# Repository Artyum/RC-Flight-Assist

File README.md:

# RC Flight Assist (RCFA) Telemetry System

RCFA is a telemetry system for RC pilots, designed specifically for outdoor pattern flying, such as F3A or F3M classes. The system provides better control over the airplane during acrobatics by implementing a radio telemetry mechanism that accurately indicates the position within the flight area. With RCFA, pilots can maintain the proper position in the sky, resulting in better handling and improved skills. The system was tested in collaboration with the top Polish F3A pilot of 2015.

#### How Does It Work?

The RCFA system comprises two separate electronic devices: the Transmitter and the Receiver. The primary role of the Transmitter is to get the 3D or 2D position from GPS and altimeter sensors and send the data to the pilot’s Receiver. The Receiver converts the signal into sound patterns, which the pilot can hear through the built-in speaker or headphones to receive telemetry information.

The basic usage of the RCFA involves defining two points on the ground to determine the flight area. The first point (P1) is the pilot’s position, where the airplane will be controlled from. The second point (P2) is the direction to the flight line where the airplane shall be controlled. These points can be set by walking with the RCFA to the desired positions on the airfield or by writing the coordinates in the configuration file (rcfa.ini). The optimal distance between P1 and P2 depends on GPS signal strength and usually does not need to be more than 20m.

#### Setting Up the Flight Area

Once points P1 and P2 are set within the Transmitter, the RCFA system automatically calculates the remaining flight area coordinates based on preset options: the ideal Flight Line (marked with points A, B, and C), the Green Zone (green color), and the Flight Area (blue color). The pilot’s job is to keep the airplane between the green rectangles.

During a flight, the RCFA Receiver generates tones that change according to the airplane’s distance from the Green Zone. This allows the pilot to react quickly and steer the airplane to the desired position in the sky. The pilot will know exactly how far the airplane is from the flight line, and whether it is ahead or behind the Green Zone, too high, or too far to the left or right side of the Flight Area.

#### Post-Flight Scoring

When the flight is over, the system calculates a score based on the time spent in the zone and overall flight time. This score is automatically stored in a KML file. The logger file can be opened instantly in Google Earth (Windows or Linux) to examine the flight and check the scoring.

#### Additional Features of the RCFA

**GPS Logger**: The system is highly customizable. Users can change various parameters such as the distance from the pilot to the flight line, area angle, flight plane width, and more (nearly 30 options). It has an integrated MicroSD slot for a memory card, which is used to store and read area parameters and to write position data as a high-accuracy GPS Logger. The system implements unique filter algorithms, ensuring high accuracy in the GPS data stream and altitude measurements. The RCFA also allows the use of a barometer for even more accurate altitude measurement. The Logger writes data directly in KML format, which can be instantly opened in Google Earth.

**Real-Time Tracking**: The RCFA can stream data to the Receiver about current 3D coordinates through the RX/TX interface (USB2TTL). The data stream (longitude, latitude, and altitude) can be read and visualized on a PC in real-time. Depending on barometer availability, the altitude data can be taken from GPS or barometer. Users can choose either absolute (mean sea level) or relative (to the pilot’s position) altitude readings.

**Variometer**: The RCFA includes a variometer feature, which can be used in gliders and other types of RC airplanes. The variometer can use GPS data or a barometer to indicate altitude changes. The data is sent to the Receiver, allowing the pilot to control descending or ascending in real-time.

# Overview
https://www.youtube.com/watch?v=m0nCrscLPIs

#### RC Flight Assist - Real-time tracking demo
https://www.youtube.com/watch?v=_wvuzFEu3uk

## Full Features List

The list of configurable parameters:
* Distance in meters between the Pilot and the Flight Line
* Area angle in degrees
* Flight Area width
* Flight line width
* Flight Area boundary alarm (Out-Of-Area)
* Altitude alarm
* Set points P1 and P2 manually
* Automatic Flight Area lock
* Real-time tracking
* Automatic reference altitude
* Manual setting of reference altitude
* GPS sample rate in 'Reads Per Second'
* GPS Logger Automatic mode
* GPS Logger Manual mode (free flight)
* Logger speed frequency
* Four different modes of Floor option
* "Low accuracy" information feature
* Configurable filtering algorithm for GPS, Altimeter, and Variometer
* Radio module switch
* Altimeter switch
* Variometer mode
* (Variometer) Minimum vertical speed ratio
* (Variometer) Maximum vertical speed ratio
* Time zone relative to UTC
* Initial sound volume in the Receiver
* Event log

### GPS Logger

RC Flight Assist can be used as a GPS Logger. The data is stored on a Micro SD card in KML format, which can be opened directly in Google Earth. The flight path is visualized as a line in 3D space as an animated track. The logger is controlled by several options:

1. **Stream Speed Frequency**: The coordinates can be saved every 0.5 to 60 seconds.
2. **GPS Data Acquiring Speed**: The data can be acquired 1, 5, or 10 times per second.
3. **Reference Altitude**: You can manually set the accurate reference altitude to ensure the plot is at the exact height. The altitude measurement relies on the high-accuracy barometer sensor MPL3115A2. If the barometer is not used, the altitude data is acquired from GPS.

The Logger can work in two modes:

**Automatic Mode**: Designed for acrobatic flights, so the pilot does not have to remember to enable or disable the Logger before each flight. The logger will start when the airplane flies into the flight zone and stop when leaving it.

**Manual Mode**: Along with the attached barometer, this makes RCFA a high-quality GPS Logger. In this mode, the Logger must be enabled and disabled manually by pressing the relevant buttons on the transmitter. To reduce energy drain, the radio module can be turned off.

### Real-time Tracking

The RC Flight Assist (RCFA) system is capable of sending position data to the Receiver in real-time. This data stream can be visualized on a PC directly in Google Earth. Currently, Google Earth has limited capabilities for displaying altitude in real-time mode. However, several third-party applications, such as GooPs (goopstechnologies.com) or EarthBridge (mboffin.com/earthbridge), can work as extensions to Google Earth to enhance its real-time tracking capabilities.

### Technical Details

**Radio Frequency**: 433MHz, 868MHz, 915MHz  
**Frequency-Hopping Spread Spectrum (FHSS)**  
**Range**: 700+/-100m (tested in open air with copper wire antenna)  
**Input Voltage**: 7-12V (2S/3S LiPo)  
**GPS Compatibility**: Global Top (MT3318, MT3329, MT3339), u-Blox (M7, M8)

#### Receiver (RX)
* **Headphones**: 3.5mm jack port
* **Average Current**: 50mA
* **Size**: 51 x 38mm
* **Weight**: ~17g

#### Transmitter (TX)
* **MicroSD Card**: 256MB-32GB class 4 (FAT32)
* **Maximum Transmit Power**: 20dB (100mW)
* **Average Current**: 150mA
* **Size**: 52 x 40mm

### Variometer

The RCFA Telemetry System can function as a variometer, providing real-time altitude data sourced from the GPS module or barometer (if available). Barometric altitude readings generally offer higher quality, but certain GPS modules such as u-Blox M8 or M7 series can also provide excellent 3D positioning signals. This telemetry system enables pilots to control ascents and descents in real-time from the ground. Specific sound patterns emitted by the receiver indicate altitude changes.

#### Customization Options

The variometer mode is highly customizable:
- **Low Pass**: Defines the minimum altitude change considered as horizontal flight.
- **High Pass**: Sets the altitude change threshold that triggers sound gradation in the speaker.

This flexibility allows pilots to tailor the variometer's responsiveness to their specific flying needs and preferences.

## RC Flight Assist (RCFA) Kit Components

#### 1. Transmitter
- **Description**: The transmitter module of the RCFA system is responsible for sending the aircraft's position data to the receiver. It gathers data from the GPS and altimeter sensors, then transmits this information using a specified radio frequency.
- **Key Features**:
  - Frequency-hopping spread spectrum (FHSS) support
  - Compatible with multiple GPS modules
  - Configurable transmission power

#### 2. Receiver
- **Description**: The receiver module receives position data from the transmitter and converts it into audible signals for the pilot. It helps in maintaining the aircraft within the designated flight area by providing real-time feedback.
- **Key Features**:
  - Headphone jack for audio feedback
  - Real-time tracking capability
  - Configurable sound patterns for various flight conditions

#### 3. GPS
- **Description**: The GPS module provides the necessary positional data for the RCFA system. It can determine the 2D or 3D position of the aircraft and relay this information to the transmitter.
- **Key Features**:
  - High compatibility (Global Top MT3318, MT3329, MT3339, u-Blox M7, M8 series)
  - Supports logging of satellite data
  - Provides accurate altitude data with the option to use a barometer for enhanced accuracy

#### 4. UART USB
- **Description**: The UART USB interface is used for configuring the RCFA system and for data logging purposes. It allows for easy communication between the RCFA modules and a PC for setup and data transfer.
- **Key Features**:
  - Enables configuration of system parameters via `rcfa.ini`
  - Facilitates firmware updates and debugging
  - Supports real-time data visualization on a PC using compatible software like Google Earth

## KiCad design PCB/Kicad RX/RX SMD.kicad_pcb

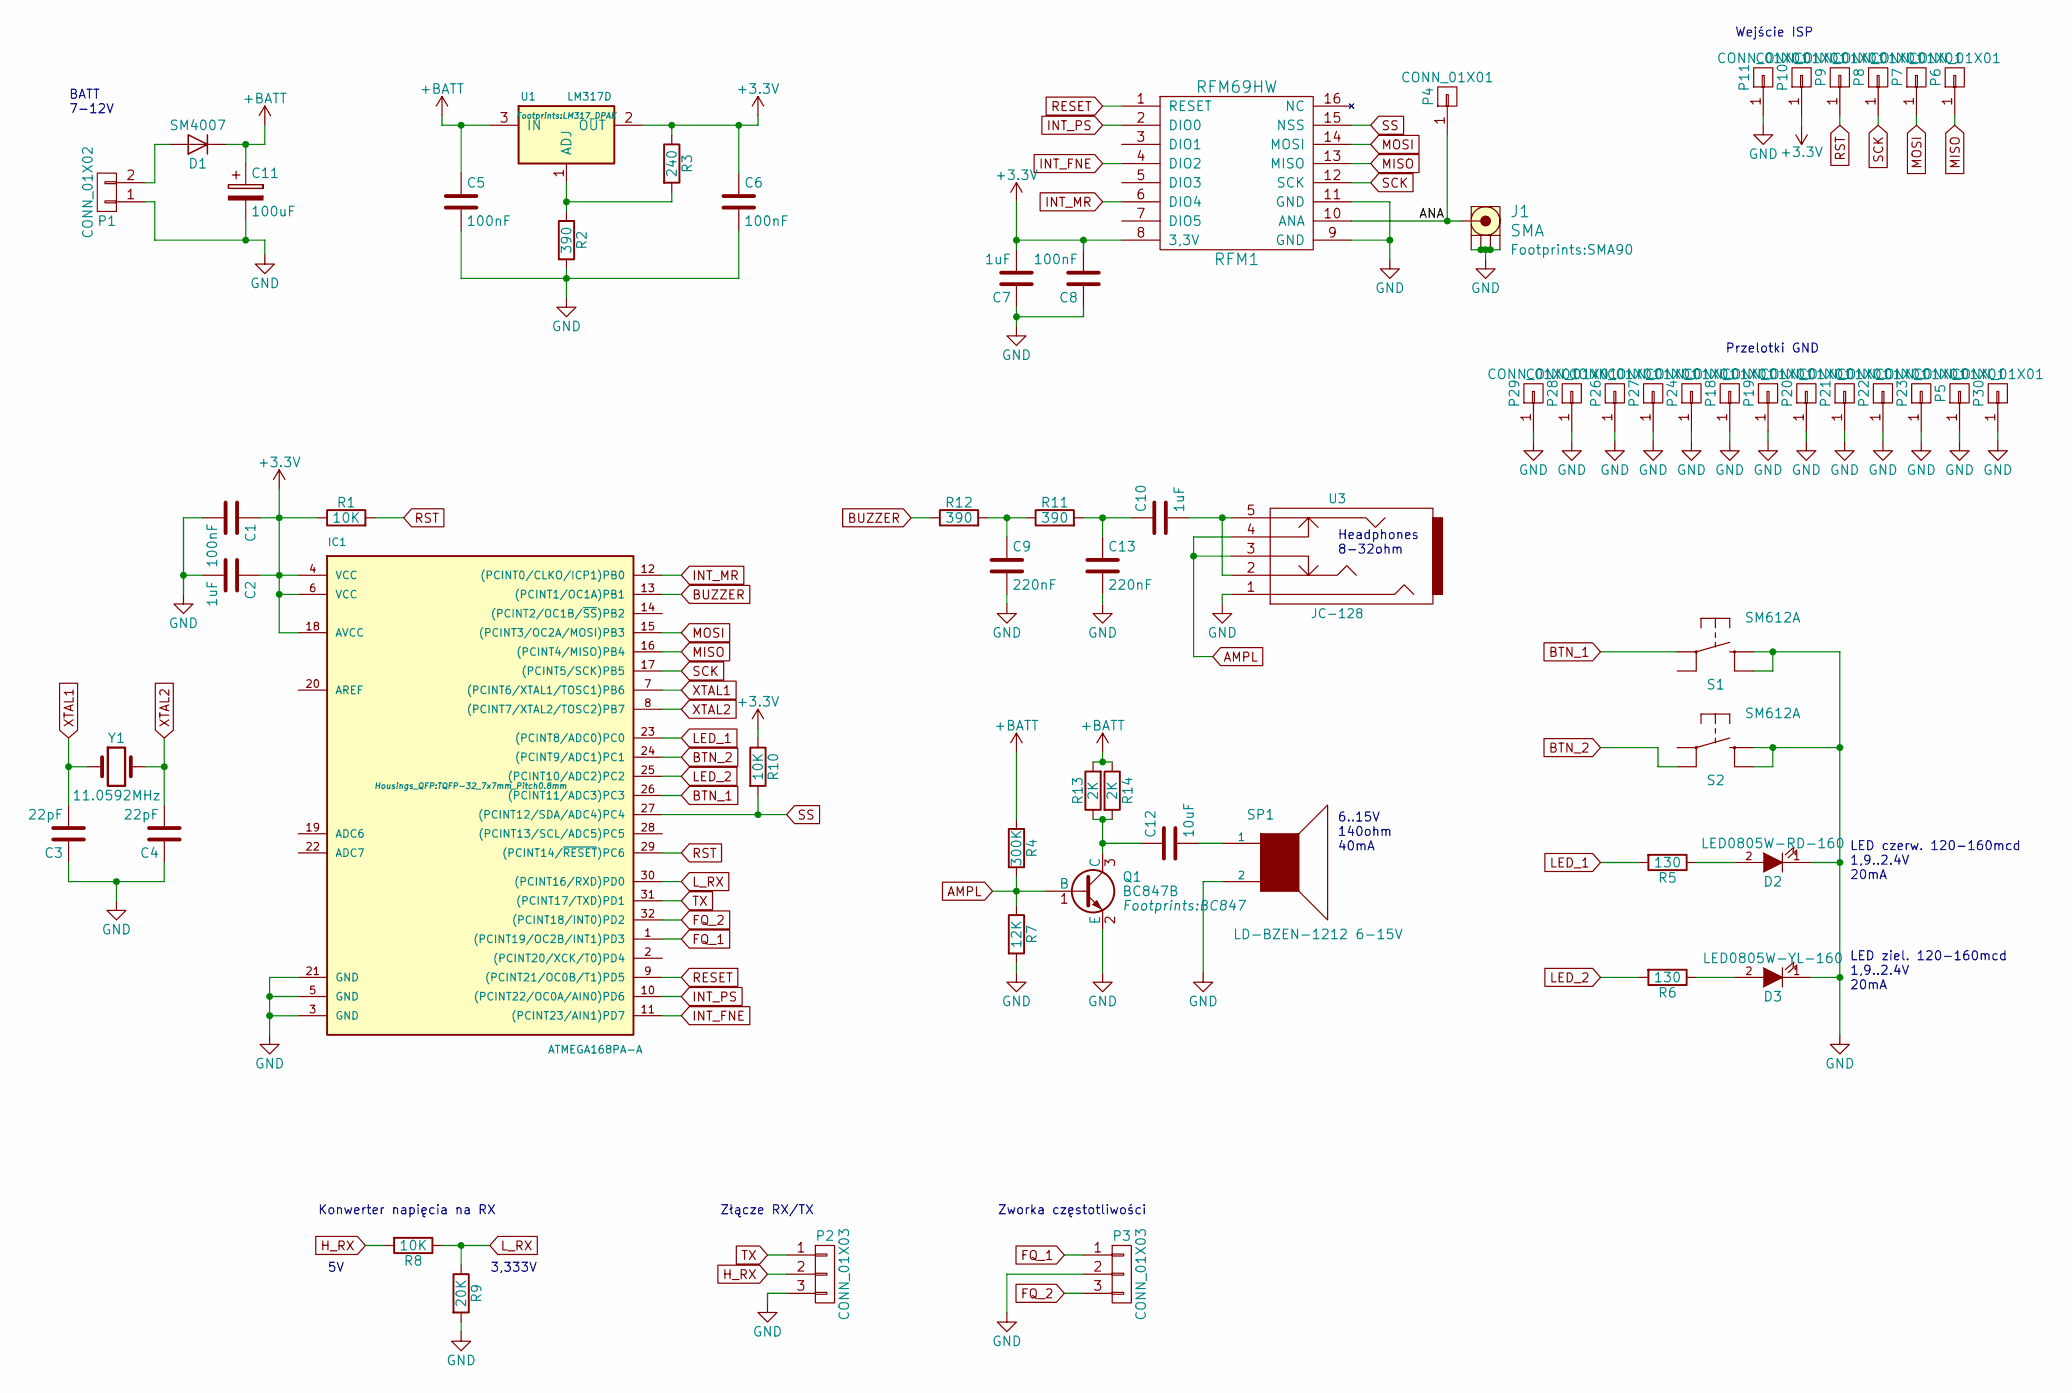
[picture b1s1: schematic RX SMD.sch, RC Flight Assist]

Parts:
C1, C5, C6, C8: 100nF; C_0805
C2, C7, C10: 1uF; C_0805
C3, C4: 22pF; C_0805
C9, C13: 220nF; C_0805
C11: 100uF; c_elec_6.3x5.3
C12: 10uF; C_0805
D1: SM4007; MELF_Standard
D2: LED0805W-RD-160; LED_0805
D3: LED0805W-YL-160; LED_0805
IC1: ATMEGA168PA-A; TQFP-32_7x7mm_Pitch0.8mm
J1: SMA; SMA90
P1: CONN_01X02; Pin_Header_Angled_1x02
P2, P3: CONN_01X03; Pin_Header_Angled_1x03
P4, P5, P6, P7, P8, P9, P10, P11, P18, P19, P20, P21, P22, P23, P24, P26, P27, P28, P29, P30: CONN_01X01; 1Pin
Q1: BC847B; BC847
R1, R8, R10: 10K; R_0805
R2, R11, R12: 390; R_0805
R3: 240; R_0805
R4: 300K; R_0805
R5, R6: 130; R_0805
R7: 12K; R_0805
R9: 20K; R_0805
R13, R14: 2K; R_0805
RFM1: RFM69HW; RFM69HW_SMD
S1, S2: SM612A; B3F_10XX
SP1: LD-BZEN-1212 6-15V; BUZZER_12x6.5
U1: LM317D; LM317_DPAK
U3: JC-128
Y1: 11.0592MHz; Crystal_HC49-U_Vertical

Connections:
+3V3: C1.1, C2.1, C6.1, C7.2, C8.2, IC1.4 (VCC), IC1.6 (VCC), IC1.18 (AVCC), P10.1, R1.1, R3.1, R10.1, RFM1.8 (3,3V), U1.2 (OUT)
+BATT: C5.1, C11.1, D1.1 (K), R4.1, R13.2, R14.1, U1.3 (IN)
/ANA: J1.1 (RF), P4.1, RFM1.10 (ANA)
AMPL: Q1.1 (B), R4.2, R7.1, U3.3, U3.4
BTN_1: IC1.26 ((PCINT11/ADC3)PC3), S1.3
BTN_2: IC1.24 ((PCINT9/ADC1)PC1), S2.4 (P1)
BUZZER: IC1.13 ((PCINT1/OC1A)PB1), R12.1
FQ_1: IC1.1 ((PCINT19/OC2B/INT1)PD3), P3.1
FQ_2: IC1.32 ((PCINT18/INT0)PD2), P3.3
GND: C1.2, C2.2, C3.1, C4.1, C5.2, C6.2, C7.1, C8.1, C9.2, C11.2, C13.2, D2.1 (K), D3.1 (K), IC1.3 (GND), IC1.5 (GND), IC1.21 (GND), J1.2 (GND1), J1.3 (GND2), J1.4 (GND3), J1.5 (GND4), P1.1, P2.3, P3.2, P5.1, P11.1, P18.1, P19.1, P20.1, P21.1, P22.1, P23.1, P24.1, P26.1, P27.1, P28.1, P29.1, P30.1, Q1.2 (E), R2.2, R7.2, R9.2, RFM1.9 (GND), RFM1.11 (GND), S1.1 (S), S1.2 (S1), S2.1 (S), S2.2 (S1), SP1.2, U3.1
H_RX: P2.2, R8.2
INT_FNE: IC1.11 ((PCINT23/AIN1)PD7), RFM1.4 (DIO2)
INT_MR: IC1.12 ((PCINT0/CLKO/ICP1)PB0), RFM1.6 (DIO4)
INT_PS: IC1.10 ((PCINT22/OC0A/AIN0)PD6), RFM1.2 (DIO0)
LED_1: IC1.23 ((PCINT8/ADC0)PC0), R5.2
LED_2: IC1.25 ((PCINT10/ADC2)PC2), R6.2
L_RX: IC1.30 ((PCINT16/RXD)PD0), R8.1, R9.1
MISO: IC1.16 ((PCINT4/MISO)PB4), P6.1, RFM1.13 (MISO)
MOSI: IC1.15 ((PCINT3/OC2A/MOSI)PB3), P7.1, RFM1.14 (MOSI)
unnamed: C9.1, R11.1, R12.2
unnamed: C10.1, C13.1, R11.2
unnamed: C10.2, U3.2, U3.5
unnamed: C12.1, Q1.3 (C), R13.1, R14.2
unnamed: C12.2, SP1.1
unnamed: D1.2 (A), P1.2
unnamed: D2.2 (A), R5.1
unnamed: D3.2 (A), R6.1
unnamed: R2.1, R3.2, U1.1 (ADJ)
RESET: IC1.9 ((PCINT21/OC0B/T1)PD5), RFM1.1 (RESET)
RST: IC1.29 ((PCINT14/~RESET~)PC6), P9.1, R1.2
SCK: IC1.17 ((PCINT5/SCK)PB5), P8.1, RFM1.12 (SCK)
SS: IC1.27 ((PCINT12/SDA/ADC4)PC4), R10.2, RFM1.15 (NSS)
TX: IC1.31 ((PCINT17/TXD)PD1), P2.1
XTAL1: C3.2, IC1.7 ((PCINT6/XTAL1/TOSC1)PB6), Y1.1
XTAL2: C4.2, IC1.8 ((PCINT7/XTAL2/TOSC2)PB7), Y1.2

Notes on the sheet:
LED czerw. 120-160mcd 1,9..2.4V 20mA
LED ziel. 120-160mcd 1,9..2.4V 20mA
Złącze RX/TX
Zworka częstotliwości
Konwerter napięcia na RX
BATT 7-12V
6..15V 140ohm 40mA
Headphones 8-32ohm
Wejście ISP
3,333V
Przelotki GND

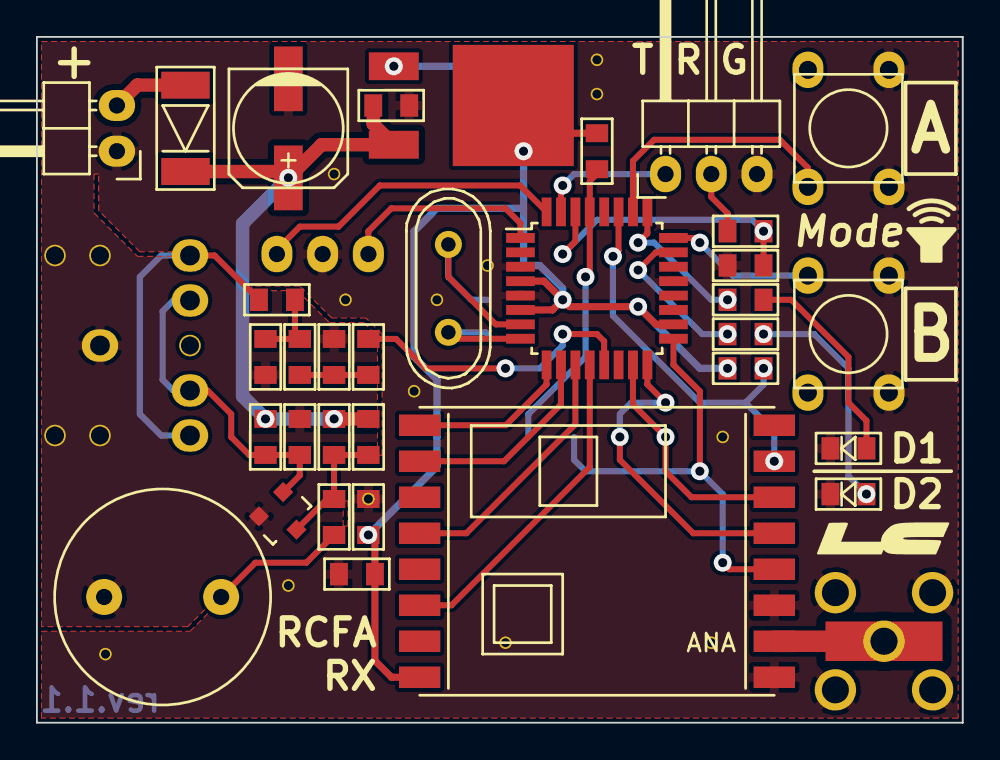
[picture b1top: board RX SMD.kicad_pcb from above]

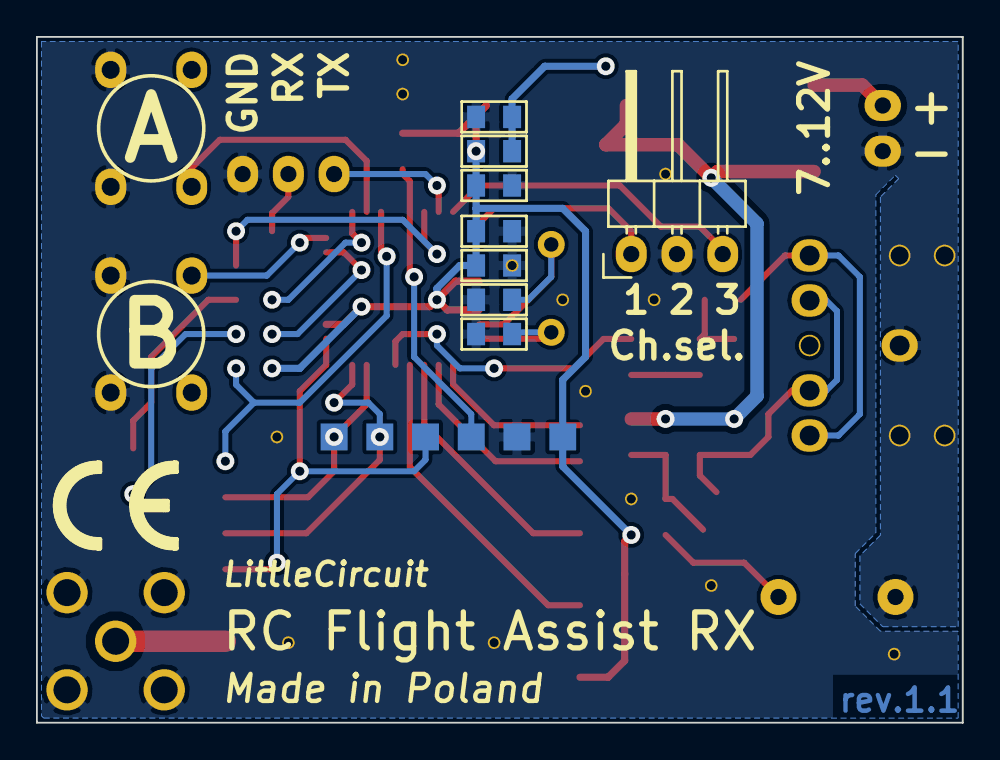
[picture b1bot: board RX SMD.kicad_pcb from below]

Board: 2 copper layers, 51.4 x 38.1 mm, 63 parts (8 on the bottom side), 35 nets.

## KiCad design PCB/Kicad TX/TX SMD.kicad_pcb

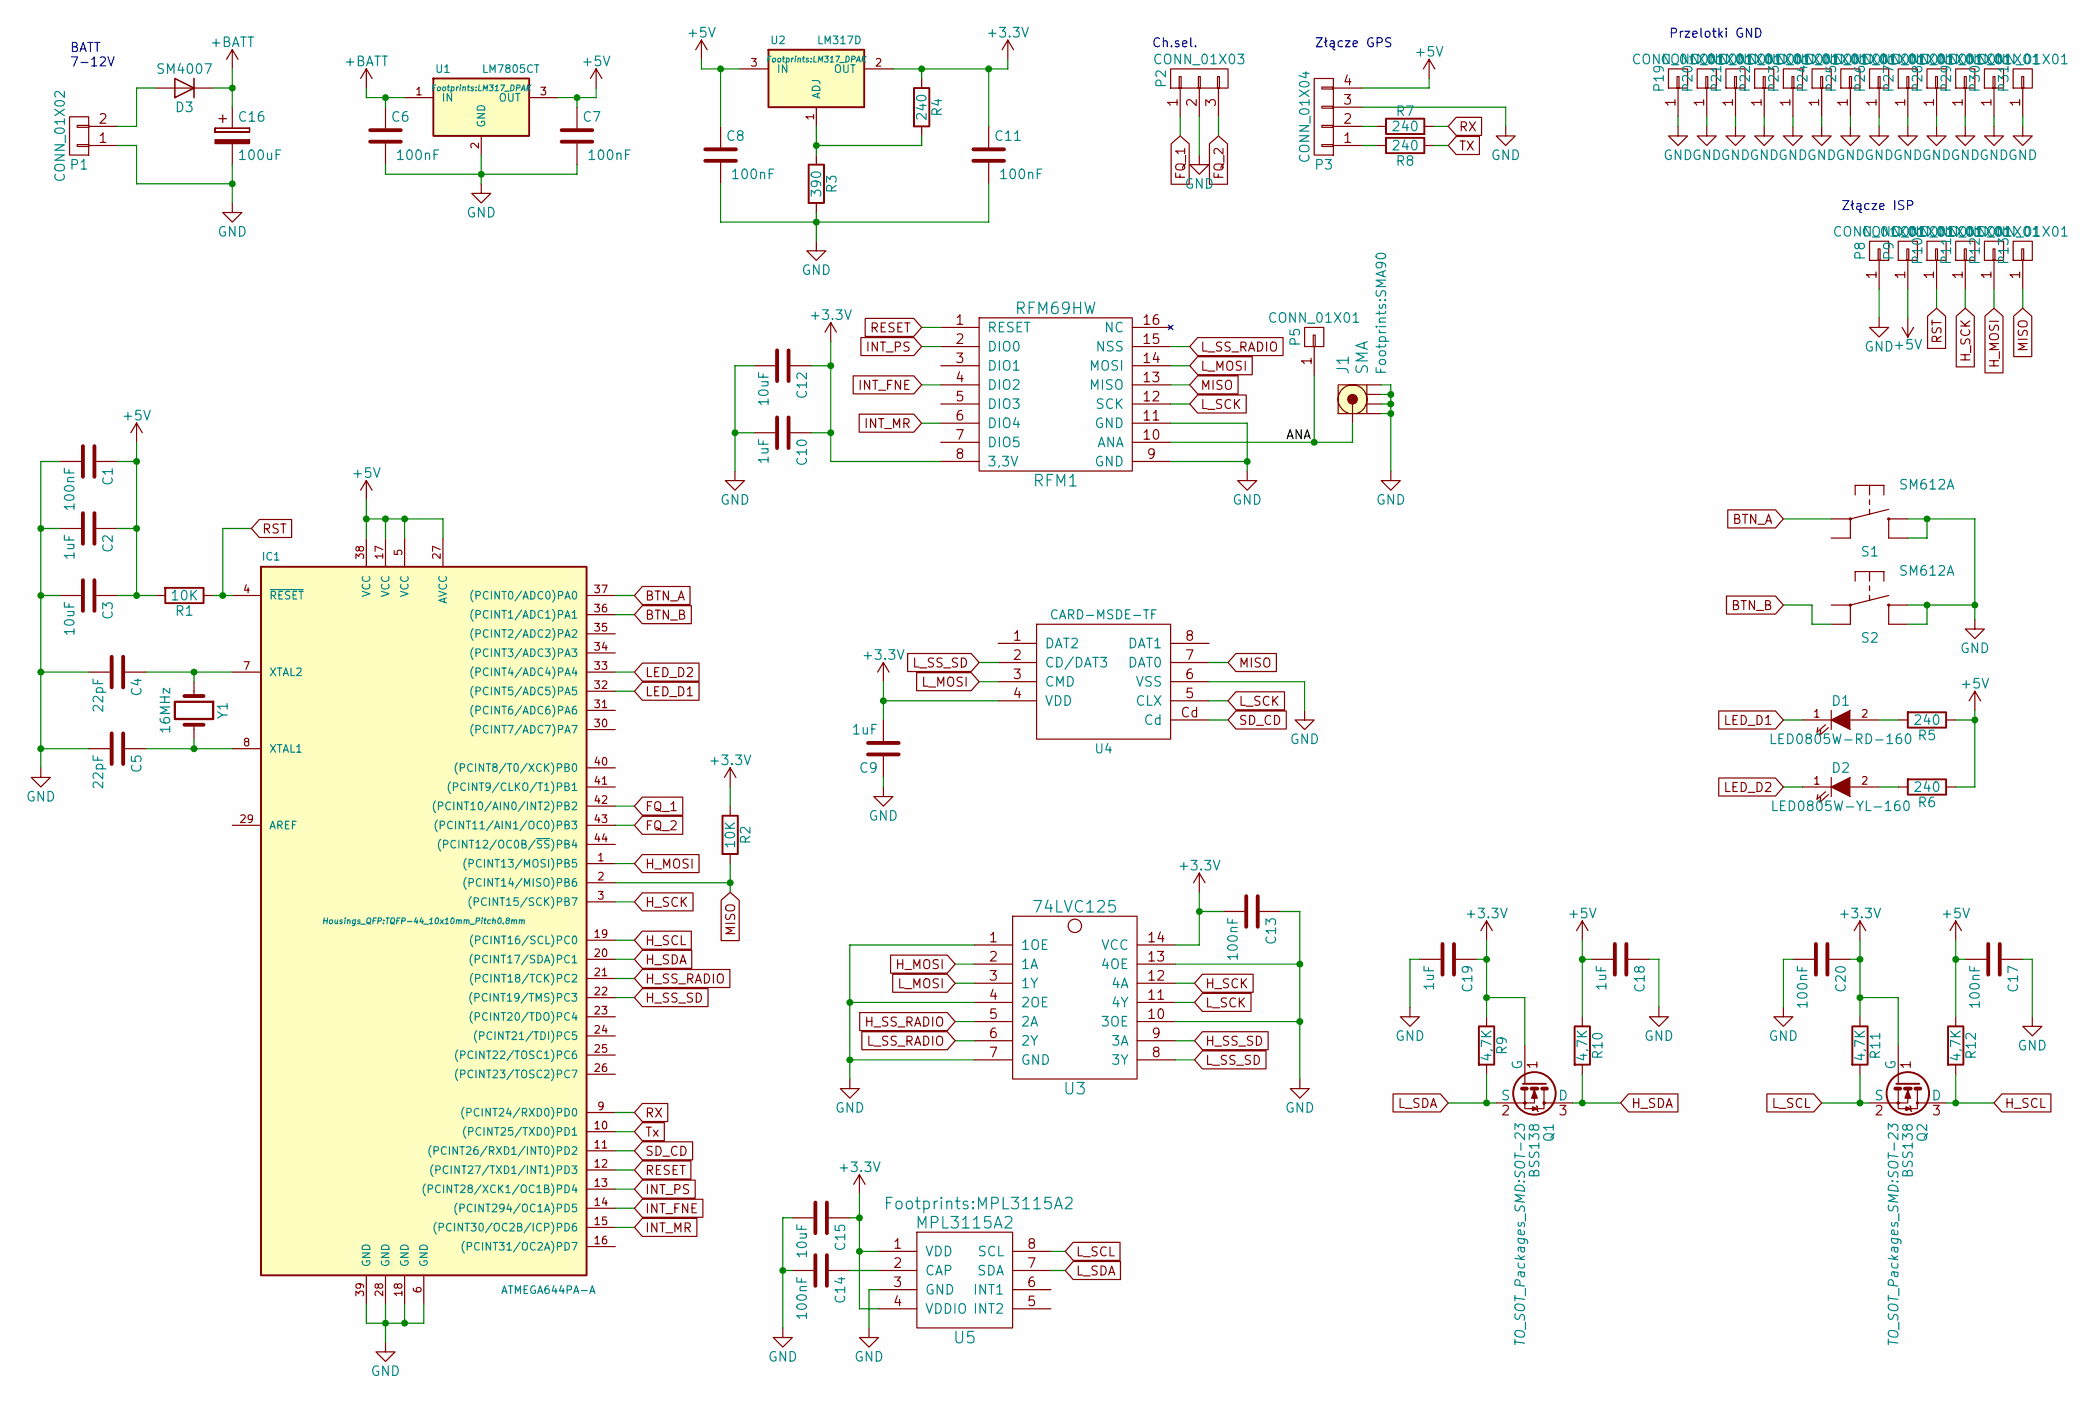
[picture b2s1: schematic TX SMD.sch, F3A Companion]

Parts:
C1, C6, C7, C8, C11, C13, C14, C17, C20: 100nF; C_0805
C2, C9, C10, C18, C19: 1uF; C_0805
C3, C12, C15: 10uF; C_0805
C4, C5: 22pF; C_0805
C16: 100uF; c_elec_6.3x5.3
D1: LED0805W-RD-160; LED_0805
D2: LED0805W-YL-160; LED_0805
D3: SM4007; MELF_Standard
IC1: ATMEGA644PA-A; TQFP-44_10x10mm_Pitch0.8mm
J1: SMA; SMA90
P1: CONN_01X02; Pin_Header_Angled_1x02
P2: CONN_01X03; Pin_Header_Angled_1x03
P3: CONN_01X04; Pin_Header_Angled_1x04
P5, P8, P9, P10, P11, P12, P13, P19, P20, P21, P22, P23, P24, P25, P26, P27, P28, P29, P30, P31: CONN_01X01; 1Pin
Q1, Q2: BSS138; SOT-23
R1, R2: 10K; R_0805
R3: 390; R_0805
R4, R5, R6, R7, R8: 240; R_0805
R9, R10, R11, R12: 4,7K; R_0805
RFM1: RFM69HW; RFM69HW_SMD
S1, S2: SM612A; B3F_10XX
U1: LM7805CT; LM317_DPAK
U2: LM317D; LM317_DPAK
U3: 74LVC125; SOIC-14_N
U4: CARD-MSDE-TF; Micro_SD_msde-tf
U5: MPL3115A2
Y1: 16MHz; Crystal_HC49-U_Vertical

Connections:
+3V3: C9.2, C10.1, C11.1, C12.1, C13.2, C15.1, C19.1, C20.1, Q1.1 (G), Q2.1 (G), R2.1, R4.1, R9.1, R11.1, RFM1.8 (3,3V), U2.2 (OUT), U3.14 (VCC), U4.4 (VDD), U5.1 (VDD), U5.4 (VDDIO)
+5V: C1.1, C2.1, C3.1, C7.1, C8.1, C17.2, C18.2, IC1.5 (VCC), IC1.17 (VCC), IC1.27 (AVCC), IC1.38 (VCC), P3.4, P9.1, R1.2, R5.1, R6.1, R10.1, R12.1, U1.3 (OUT), U2.3 (IN)
+BATT: C6.1, C16.1, D3.1 (K), U1.1 (IN)
/ANA: J1.1 (RF), P5.1, RFM1.10 (ANA)
BTN_A: IC1.37 ((PCINT0/ADC0)PA0), S1.3
BTN_B: IC1.36 ((PCINT1/ADC1)PA1), S2.4 (P1)
FQ_1: IC1.42 ((PCINT10/AIN0/INT2)PB2), P2.1
FQ_2: IC1.43 ((PCINT11/AIN1/OC0)PB3), P2.3
GND: C1.2, C2.2, C3.2, C4.2, C5.2, C6.2, C7.2, C8.2, C9.1, C10.2, C11.2, C12.2, C13.1, C14.2, C15.2, C16.2, C17.1, C18.1, C19.2, C20.2, IC1.6 (GND), IC1.18 (GND), IC1.28 (GND), IC1.39 (GND), J1.2 (GND1), J1.3 (GND2), J1.4 (GND3), J1.5 (GND4), P1.1, P2.2, P3.3, P8.1, P19.1, P20.1, P21.1, P22.1, P23.1, P24.1, P25.1, P26.1, P27.1, P28.1, P29.1, P30.1, P31.1, R3.2, RFM1.9 (GND), RFM1.11 (GND), S1.1 (S), S1.2 (S1), S2.1 (S), S2.2 (S1), U1.2 (GND), U3.1 (1OE), U3.4 (2OE), U3.7 (GND), U3.10 (3OE), U3.13 (4OE), U4.6 (VSS), U5.3 (GND)
H_MOSI: IC1.1 ((PCINT13/MOSI)PB5), P12.1, U3.2 (1A)
H_SCK: IC1.3 ((PCINT15/SCK)PB7), P11.1, U3.12 (4A)
H_SCL: IC1.19 ((PCINT16/SCL)PC0), Q2.3 (D), R12.2
H_SDA: IC1.20 ((PCINT17/SDA)PC1), Q1.3 (D), R10.2
H_SS_RADIO: IC1.21 ((PCINT18/TCK)PC2), U3.5 (2A)
H_SS_SD: IC1.22 ((PCINT19/TMS)PC3), U3.9 (3A)
INT_FNE: IC1.14 ((PCINT294/OC1A)PD5), RFM1.4 (DIO2)
INT_MR: IC1.15 ((PCINT30/OC2B/ICP)PD6), RFM1.6 (DIO4)
INT_PS: IC1.13 ((PCINT28/XCK1/OC1B)PD4), RFM1.2 (DIO0)
LED_D1: D1.1 (K), IC1.32 ((PCINT5/ADC5)PA5)
LED_D2: D2.1 (K), IC1.33 ((PCINT4/ADC4)PA4)
L_MOSI: RFM1.14 (MOSI), U3.3 (1Y), U4.3 (CMD)
L_SCK: RFM1.12 (SCK), U3.11 (4Y), U4.5 (CLX)
L_SCL: Q2.2 (S), R11.2, U5.8 (SCL)
L_SDA: Q1.2 (S), R9.2, U5.7 (SDA)
L_SS_RADIO: RFM1.15 (NSS), U3.6 (2Y)
L_SS_SD: U3.8 (3Y), U4.2 (CD/DAT3)
MISO: IC1.2 ((PCINT14/MISO)PB6), P13.1, R2.2, RFM1.13 (MISO), U4.7 (DAT0)
unnamed: C4.1, IC1.7 (XTAL2), Y1.1
unnamed: C5.1, IC1.8 (XTAL1), Y1.2
unnamed: C14.1, U5.2 (CAP)
unnamed: D1.2 (A), R5.2
unnamed: D2.2 (A), R6.2
unnamed: D3.2 (A), P1.2
unnamed: P3.1, R8.2
unnamed: P3.2, R7.1
unnamed: R3.1, R4.2, U2.1 (ADJ)
RESET: IC1.12 ((PCINT27/TXD1/INT1)PD3), RFM1.1 (RESET)
RST: IC1.4 (~RESET), P10.1, R1.1
RX: IC1.9 ((PCINT24/RXD0)PD0), R7.2
SD_CD: IC1.11 ((PCINT26/RXD1/INT0)PD2), U4.Cd
TX: IC1.10 ((PCINT25/TXD0)PD1), R8.1

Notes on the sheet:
BATT 7-12V
Złącze GPS
Ch.sel.
Przelotki GND
Złącze ISP

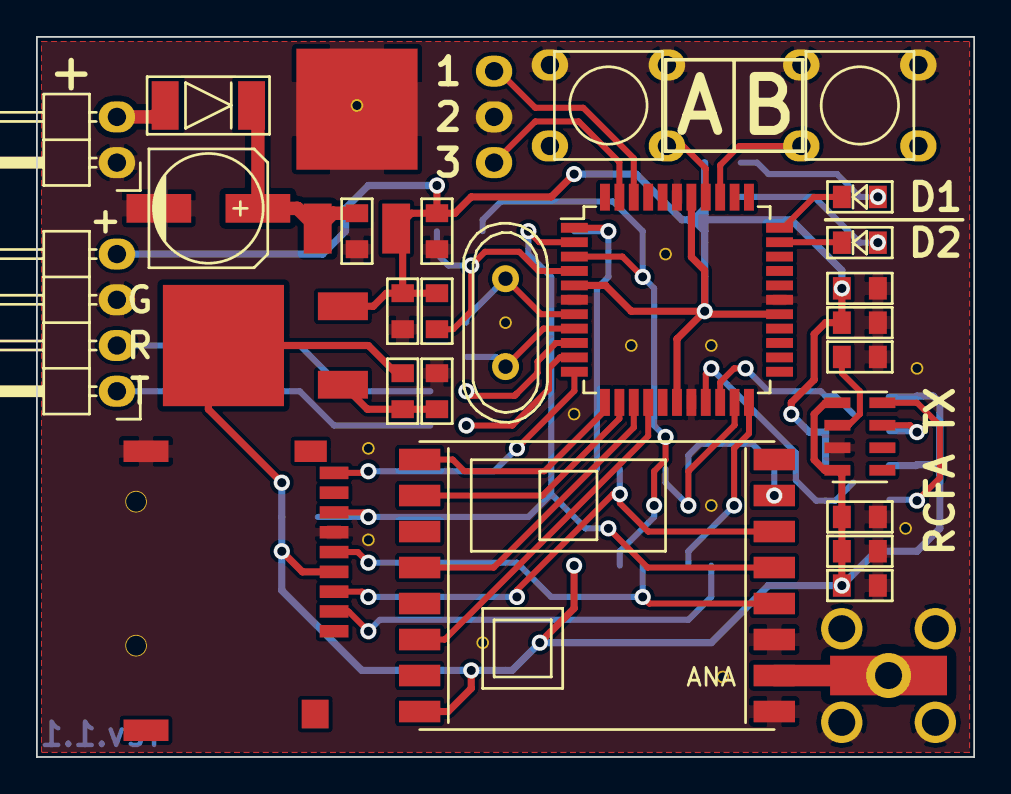
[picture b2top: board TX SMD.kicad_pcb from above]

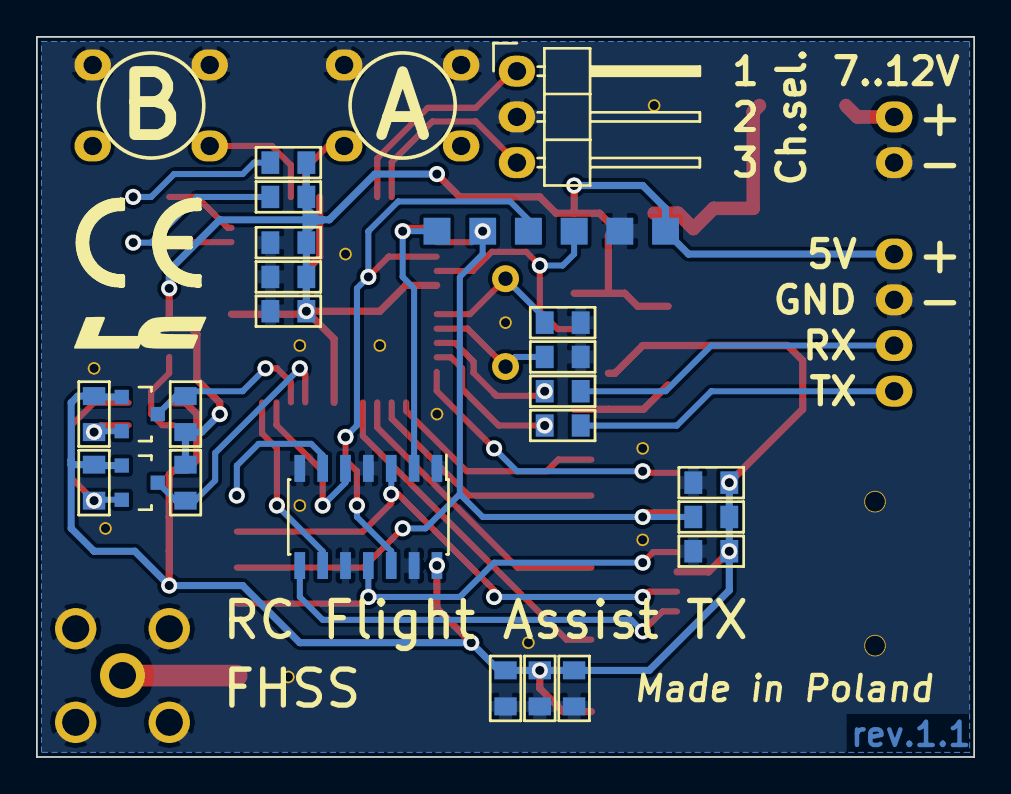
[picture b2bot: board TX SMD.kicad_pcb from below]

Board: 2 copper layers, 52.1 x 40.0 mm, 71 parts (23 on the bottom side), 41 nets.

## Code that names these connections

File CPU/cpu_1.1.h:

#ifndef _CPU_H_
#define _CPU_H_

#include "../config.h"
#include <avr/io.h>
#include "../RADIO/radio.h"

#if PCB_REVISION==1

#if CPU==0

//BUTTON
#define BTN1_DDR		DDRC
#define BTN1_PORT		PORTC
#define BTN1_PINPORT	PINC
#define BTN1_PIN		PC3
#define BTN2_DDR		DDRC
#define BTN2_PORT		PORTC
#define BTN2_PINPORT	PINC
#define BTN2_PIN		PC1

//BUZZER
#define BUZZER_DDR		DDRB
#define BUZZER_PORT		PORTB
#define BUZZER_PIN		PB1

//LED
#define LED1_DDR		DDRC
#define LED1_PORT		PORTC
#define LED1_PIN		PC0
#define LED2_DDR		DDRC
#define LED2_PORT		PORTC
#define LED2_PIN		PC2

//Radio interrupt
#define INT_DDR			DDRD
#define INT_PORT		PORTD
#define INT_PINPORT		PIND
#define INT_FNE_PIN		PD7
#define INT_CRC_PIN		PD6
#define INT_FIFO_NOT_EMPTY	(INT_PINPORT & (1<<INT_FNE_PIN))
#define INT_CRCOK			(INT_PINPORT & (1<<INT_CRC_PIN))

//Radio frequency switch
#define FQ_DDR			DDRD
#define FQ_PORT			PORTD
#define FQ_PINPORT		PIND
#define FQ_PIN_1		PD3
#define FQ_PIN_2		PD2

//SPI
#define SPI_DDR			DDRB
#define SPI_PORT		PORTB
//#define SPI_SS_PORT		PORTB
//#define SPI_SS			PB2
#define SPI_SS_ORG		PB2
#define SPI_MOSI		PB3
#define SPI_MISO		PB4
#define SPI_SCK			PB5

#define SPI_SS_DDR		DDRC
#define SPI_SS_PORT		PORTC
#define SPI_SS			PC4

#define TIMER_VECT		TIMER0_COMPA_vect

#define LED1_ON			BIT_HIGH(LED1_PORT,LED1_PIN)
#define LED1_OFF		BIT_LOW(LED1_PORT,LED1_PIN)

#define LED2_ON			BIT_HIGH(LED2_PORT,LED2_PIN)
#define LED2_OFF		BIT_LOW(LED2_PORT,LED2_PIN)

#elif CPU==1

//Button
#define BTN1_DDR		DDRA
#define BTN1_PORT		PORTA
#define BTN1_PINPORT	PINA
#define BTN1_PIN		PA0

#define BTN2_DDR		DDRA
#define BTN2_PORT		PORTA
#define BTN2_PINPORT	PINA
#define BTN2_PIN		PA1

//LED
#define LED1_DDR		DDRA
#define LED1_PORT		PORTA
#define LED1_PIN		PA4

#define LED2_DDR		DDRA
#define LED2_PORT		PORTA
#define LED2_PIN		PA5

//Radio interrupt
#define INT_DDR			DDRD
#define INT_PORT		PORTD
#define INT_PINPORT		PIND
#define INT_PS_PIN		PD4
#define INT_FNE_PIN		PD5
#define INT_MR_PIN		PD6
#define INT_PACKET_SENT		(INT_PINPORT & (1<<INT_PS_PIN))
#define INT_FIFO_NOT_EMPTY	(INT_PINPORT & (1<<INT_FNE_PIN))
#define INT_CRCOK			(INT_PINPORT & (1<<INT_CRC_PIN))

//SPI Radio
#define SPI_DDR			DDRB
#define SPI_PORT		PORTB
#define SPI_MOSI		PB5
#define SPI_MISO		PB6
#define SPI_SCK			PB7
#define SPI_SS_ORG		PB4

//SPI frequency for the radio
//#define RADIO_FCLK	SPCR = (1<<SPE)|(1<<MSTR)|(1<<SPR0)				/* F_CPU / 16 */
//#define RADIO_FCLK	SPCR = (1<<SPE)|(1<<MSTR)						/* F_CPU / 4 */

//SS
#define SPI_SS_DDR		DDRC
#define SPI_SS_PORT		PORTC
#define SPI_SS			PC2		/* SPI -> Radio */
#define SPI_SS_SD		PC3		/* SPI -> SD */

//Karta SD
#define SD_PORT			PORTD
#define SD_PIN			PIND
#define SD_CD			PD2		/* Card Detected */
//#define SD_WP			PB1		/* Write protected */

//Radio frequency switch
#define FQ_DDR			DDRB
#define FQ_PORT			PORTB
#define FQ_PINPORT		PINB
#define FQ_PIN_1		PB2
#define FQ_PIN_2		PB3

#define TIMER_VECT		TIMER0_COMPA_vect

#define SD_CS_LOW		SPI_SS_PORT &= ~(1<<SPI_SS_SD)		/* CS=low */
#define SD_CS_HIGH		SPI_SS_PORT |= (1<<SPI_SS_SD)		/* CS=high */
//#define SD_PWR_LOW	SD_PORT &= ~(1<<SD_PWR)
//#define SD_PWR_HIGH	SD_PORT |= (1<<SD_PWR)

//Card detected.   yes:true, no:false, default:true
#define SD_MMC_CD		(!(SD_PIN & (1<<SD_CD)))

//Write protected. yes:true, no:false, default:false
//#define SD_MMC_WP		(SD_PIN & (1<<SD_WP))
#define SD_MMC_WP		0

//SPI frequency for SD
//#define SD_FCLK_SLOW	SPCR = (1<<SPE)|(1<<MSTR)|(1<<SPR1)|(1<<SPR0)	/* F_CPU / 128 */
//#define SD_FCLK_SLOW	SPCR = (1<<SPE)|(1<<MSTR)|(1<<SPR1)				/* F_CPU / 64 */
//#define SD_FCLK_SLOW	SPCR = (1<<SPE)|(1<<MSTR)|(1<<SPR0)				/* F_CPU / 16 */

//#define SD_FCLK_FAST	SPCR = (1<<SPE)|(1<<MSTR)|(1<<SPR1)				/* F_CPU / 128 */
//#define SD_FCLK_FAST	SPCR = (1<<SPE)|(1<<MSTR)|(1<<SPR1)				/* F_CPU / 64 */
//#define SD_FCLK_FAST	SPCR = (1<<SPE)|(1<<MSTR)|(1<<SPR0)				/* F_CPU / 16 */
//#define SD_FCLK_FAST	SPCR = (1<<SPE)|(1<<MSTR)						/* F_CPU / 4 */

#define LED1_ON			BIT_LOW(LED1_PORT,LED1_PIN)
#define LED1_OFF		BIT_HIGH(LED1_PORT,LED1_PIN)

#define LED2_ON			BIT_LOW(LED2_PORT,LED2_PIN)
#define LED2_OFF		BIT_HIGH(LED2_PORT,LED2_PIN)

#endif

// ************************************************************************************************************* //
// Macros and definitions

#define BIT_LOW(PORT,PIN)		PORT &= ~(1<<PIN)
#define BIT_HIGH(PORT,PIN)		PORT |= (1<<PIN)
#define BIT_TOG(PORT,PIN)		PORT ^= (1<<PIN)
//Returns 1 if bit == 1; 0 if bit == 0
#define READ_BIT(PINPORT,PIN)	(PINPORT & (1<<PIN))

#define LED1_TOG		BIT_TOG(LED1_PORT,LED1_PIN)
#define LED2_TOG		BIT_TOG(LED2_PORT,LED2_PIN)

//The number of elements in the array
#define NUM_ELEMENTS(x)	(sizeof(x)/sizeof(x[0]))

extern volatile uint16_t t_led1;
extern volatile uint16_t t_led2;
extern uint8_t led1_status;
extern uint8_t led2_status;

void cpu_init(void);
void delay_ms(uint16_t time);

#endif
#endif /* _CPU_H_ */

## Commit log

2024-07-22 Init
2024-07-22 Audio
2024-07-23 Create LICENSE
